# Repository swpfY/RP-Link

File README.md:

## RP-Link

基于 [Picoprobe](https://github.com/raspberrypi/picoprobe) 的 [树莓派Pico](https://www.raspberrypi.com/documentation/microcontrollers/raspberry-pi-pico.html) 调试器。

- 原理图在：[RP-Link.pdf](./RP-Link.pdf)

- 实物图在： [static/RP-Link_.jpeg](./static/RP-Link_.jpeg)

- bom表在：[bom/ibom.html](./bom/ibom.html)
- genber文件在：[genber/](./genber/)

- 引脚定义如下图：

</img>

> PCB设计参考自：[raspberry pi pico](https://www.raspberrypi.com/documentation/microcontrollers/) 和 [EnvOpenPico](https://github.com/Envious-Data/EnvOpenPico)

## 更多

[使用 CLion 调试树莓派 Pico](./doc/使用CLion调试树莓派Pico.md)

生成交互式Bom表单的插件为：[InteractiveHtmlBom](https://github.com/openscopeproject/InteractiveHtmlBom)

picoprobe 可执行文件可以在 [Releases](https://github.com/swpfY/RP-Link/releases) 中找到

> 🤪目前刚入门水平有限，还在学习，后续会继续优化迭代

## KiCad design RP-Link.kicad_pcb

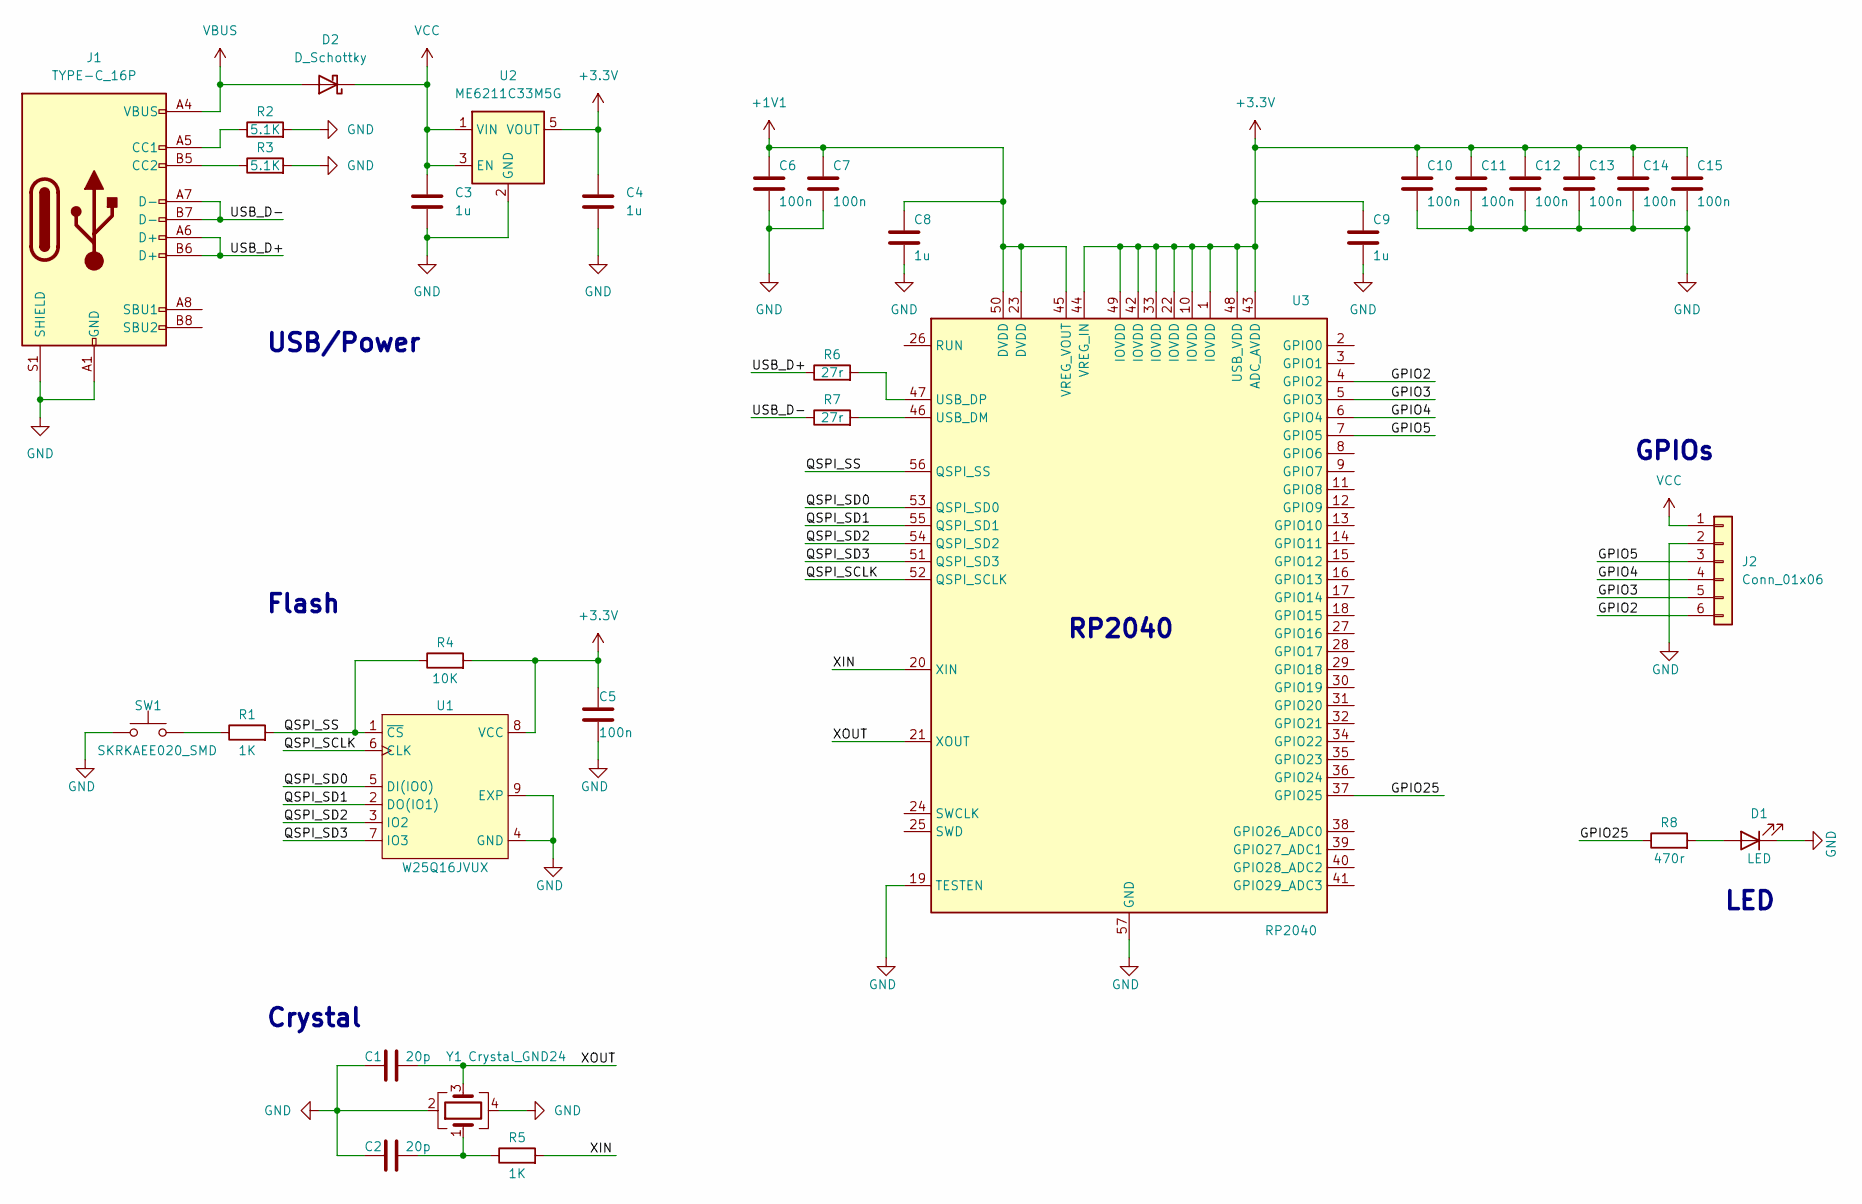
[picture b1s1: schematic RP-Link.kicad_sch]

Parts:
C1, C2: 20p; C_0402_1005Metric
C3, C4: 1u; C_0603_1608Metric
C5, C6, C7, C10, C11, C12, C13, C14, C15: 100n; C_0402_1005Metric
C8, C9: 1u; C_0402_1005Metric
D1: LED; LED_0603_1608Metric
D2: D_Schottky; D_SOD-123F
J1: TYPE-C_16P; USB_C_Receptacle_XKB_U262-16XN-4BVC11
J2: Conn_01x06; Hirose_DF13-06P-1.25DS_1x06_P1.25mm_Horizontal
R1, R5: 1K; R_0402_1005Metric
R2, R3: 5.1K; R_0402_1005Metric
R4: 10K; R_0402_1005Metric
R6, R7: 27r; R_0402_1005Metric
R8: 470r; R_0402_1005Metric
SW1: SKRKAEE020_SMD; SKRKAEE020
U1: W25Q16JVUX; USON-8_2x3mm_P0.6mm
U2: ME6211C33M5G; SOT-23-5
U3: RP2040; QFN-56-1EP_7x7mm_P0.4mm_EP3.2x3.2mm
Y1: Crystal_GND24; Crystal_SMD_3225-4Pin_3.2x2.5mm

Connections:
+1V1: C6.1, C7.1, C8.1, U3.23 (DVDD), U3.45 (VREG_VOUT), U3.50 (DVDD)
+3.3V: C4.1, C5.1, C9.1, C10.1, C11.1, C12.1, C13.1, C14.1, C15.1, R4.2, U1.8 (VCC), U2.5 (VOUT), U3.1 (IOVDD), U3.10 (IOVDD), U3.22 (IOVDD), U3.33 (IOVDD), U3.42 (IOVDD), U3.43 (ADC_AVDD), U3.44 (VREG_IN), U3.48 (USB_VDD), U3.49 (IOVDD)
/GPIO2: J2.6, U3.4 (GPIO2)
/GPIO3: J2.5, U3.5 (GPIO3)
/GPIO4: J2.4, U3.6 (GPIO4)
/GPIO5: J2.3, U3.7 (GPIO5)
/GPIO25: R8.1, U3.37 (GPIO25)
/QSPI_SCLK: U1.6 (CLK), U3.52 (QSPI_SCLK)
/QSPI_SD0: U1.5 (DI(IO0)), U3.53 (QSPI_SD0)
/QSPI_SD1: U1.2 (DO(IO1)), U3.55 (QSPI_SD1)
/QSPI_SD2: U1.3 (IO2), U3.54 (QSPI_SD2)
/QSPI_SD3: U1.7 (IO3), U3.51 (QSPI_SD3)
/QSPI_SS: R1.2, R4.1, U1.1 (~CS), U3.56 (QSPI_SS)
/USB_D+: J1.A6 (D+), J1.B6 (D+), R6.1
/USB_D-: J1.A7 (D-), J1.B7 (D-), R7.1
/XIN: R5.2, U3.20 (XIN)
/XOUT: C1.2, U3.21 (XOUT), Y1.3
GND: C1.1, C2.1, C3.2, C4.2, C5.2, C6.2, C7.2, C8.2, C9.2, C10.2, C11.2, C12.2, C13.2, C14.2, C15.2, D1.1 (K), J1.A1 (GND), J1.A12 (GND), J1.B1 (GND), J1.B12 (GND), J1.S1 (SHIELD), J2.2, R2.2, R3.2, SW1.1, U1.4 (GND), U1.9 (EXP), U2.2 (GND), U3.19 (TESTEN), U3.57 (GND), Y1.2, Y1.4
unnamed: C2.2, R5.1, Y1.1
unnamed: D1.2 (A), R8.2
unnamed: J1.A5 (CC1), R2.1
unnamed: J1.B5 (CC2), R3.1
unnamed: R1.1, SW1.2
unnamed: R6.2, U3.47 (USB_DP)
unnamed: R7.2, U3.46 (USB_DM)
VBUS: D2.2 (A), J1.A4 (VBUS), J1.A9 (VBUS), J1.B4 (VBUS), J1.B9 (VBUS)
VCC: C3.1, D2.1 (K), J2.1, U2.1 (VIN), U2.3 (EN)

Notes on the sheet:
RP2040
Crystal
Flash
USB/Power
LED
GPIOs

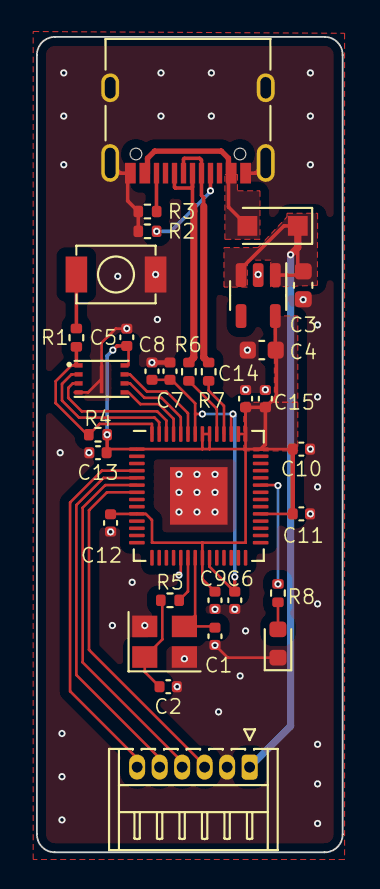
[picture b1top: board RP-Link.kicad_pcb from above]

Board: 2 copper layers, 17.0 x 45.3 mm, 32 parts (0 on the bottom side), 27 nets.

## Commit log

2022-11-08 add doc
2022-11-08 update .gitignore
    - 保留genber目录
    - 删除fp-info-cache（缓存文件）
2022-11-08 update readme
    更新文档
2022-11-08 Update README.md
    更新文档
2022-11-08 Update README.md
    更新readme
2022-11-13 修复一些问题
    #2
